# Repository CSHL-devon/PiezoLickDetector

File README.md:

# Piezo Lick Detector

An amplifier for detecting rodent licks using piezo-based sensor systems

## General Use

Each board has three channels that can receive separate input from three different piezo sensors. Each channel has independently controllable gain and dual outputs: raw analog voltage and 5V TTL.

### Piezo Concerns

- We use 12mm piezo disks that are extremely common and cheap. 

- "Positive" input on the amp is considered the crystal side of the piezo (the white center of the disk/strip) and "negative" the surrounding copper. If you wire it backwards, you will still get a signal (piezo output is AC), but it may not be the side of the signal you want. The amp cuts anything below zero as it enters the circuit, so depending on the orientation of the piezo in the sensor, or with respect to the animal, the "positive" voltage swing may be bigger, or smaller than the "negative" swing when the animal licks. Best practice is just to test output response once the system is in place and wire it the way you get the biggest signal.

- If you're solding the wires to the piezo yourself, take care not to overheat the piezo. Even if it doesn't visibly delaminate the piezo, you could do enough unseen damage to end up with a poor sensor. If you're not confident in your soldering skills, piezos are available pre-wired.

- This is a voltage-mode piezo amp. The length of the wire between the piezo and the amp should be kept to a minimum, else the capacitance of the cable will start to interfere with the sensor.

### Gain

The gain of the amplifier is adjusted using the round trimmer marked "Gain" for the appropriate channel. This trimmer is multi-turn to add some precision to the adjustments, however it has no stops to indicate the start, or end of the range. On first use, it's a good idea to simply turn it counter-clockwise several (~10) full turns to be sure you're at the bottom and then slowly work your way up until you reach the desired signal.  

Choosing the correct gain can be tricky with piezo-based systems and the quality of the detection you get will depend on the type of piezo/lick-spout you deploy, the placement of your sensor with respect to the animal and how well the sensor is physically isolated from other sources of shock/vibration. This is not trivial and takes some practice to get your setup and positioning perfect. 

### Threshold

The 5V TTL output is based on thresholding the raw voltage signal. That threshold is controlled using the square single-turn trimmer labeled "Threshold" for the appropriate channel. The available threshold does not cover the entire 0-5V range of the device. By default, it covers 2.5V-3.75V. This range was found (for our purposes) to encompass the best gain settings for noise when the setup is well optimized. You can, of course alter the range by changing the values of R2, R9 and R10 (as an example for channel 1) if you find it doesn't suit your use-case, but the default is a good starting point. You could also just bring the raw signal in through a DAQ and threshold in software if that suits your setup design.

## Building

This project came before I started converting all my projects to through-hole, so most of the parts are surface-mount. It's not too bad and If you practice a bit with a rework station you can get through it. If you have access to a surface-mount oven it's easy. Otherwise, there are many services that will populate the board with the parts for you. 

I may eventually get around to updating this to through-hole construction, but you can also just build it on a breadboard, or an Adafruit perma-proto board by following the schematic, without the custom PCB. This is probably the easiest way to get up and running for the least money and all of the parts I've used have through-hole equivalents.

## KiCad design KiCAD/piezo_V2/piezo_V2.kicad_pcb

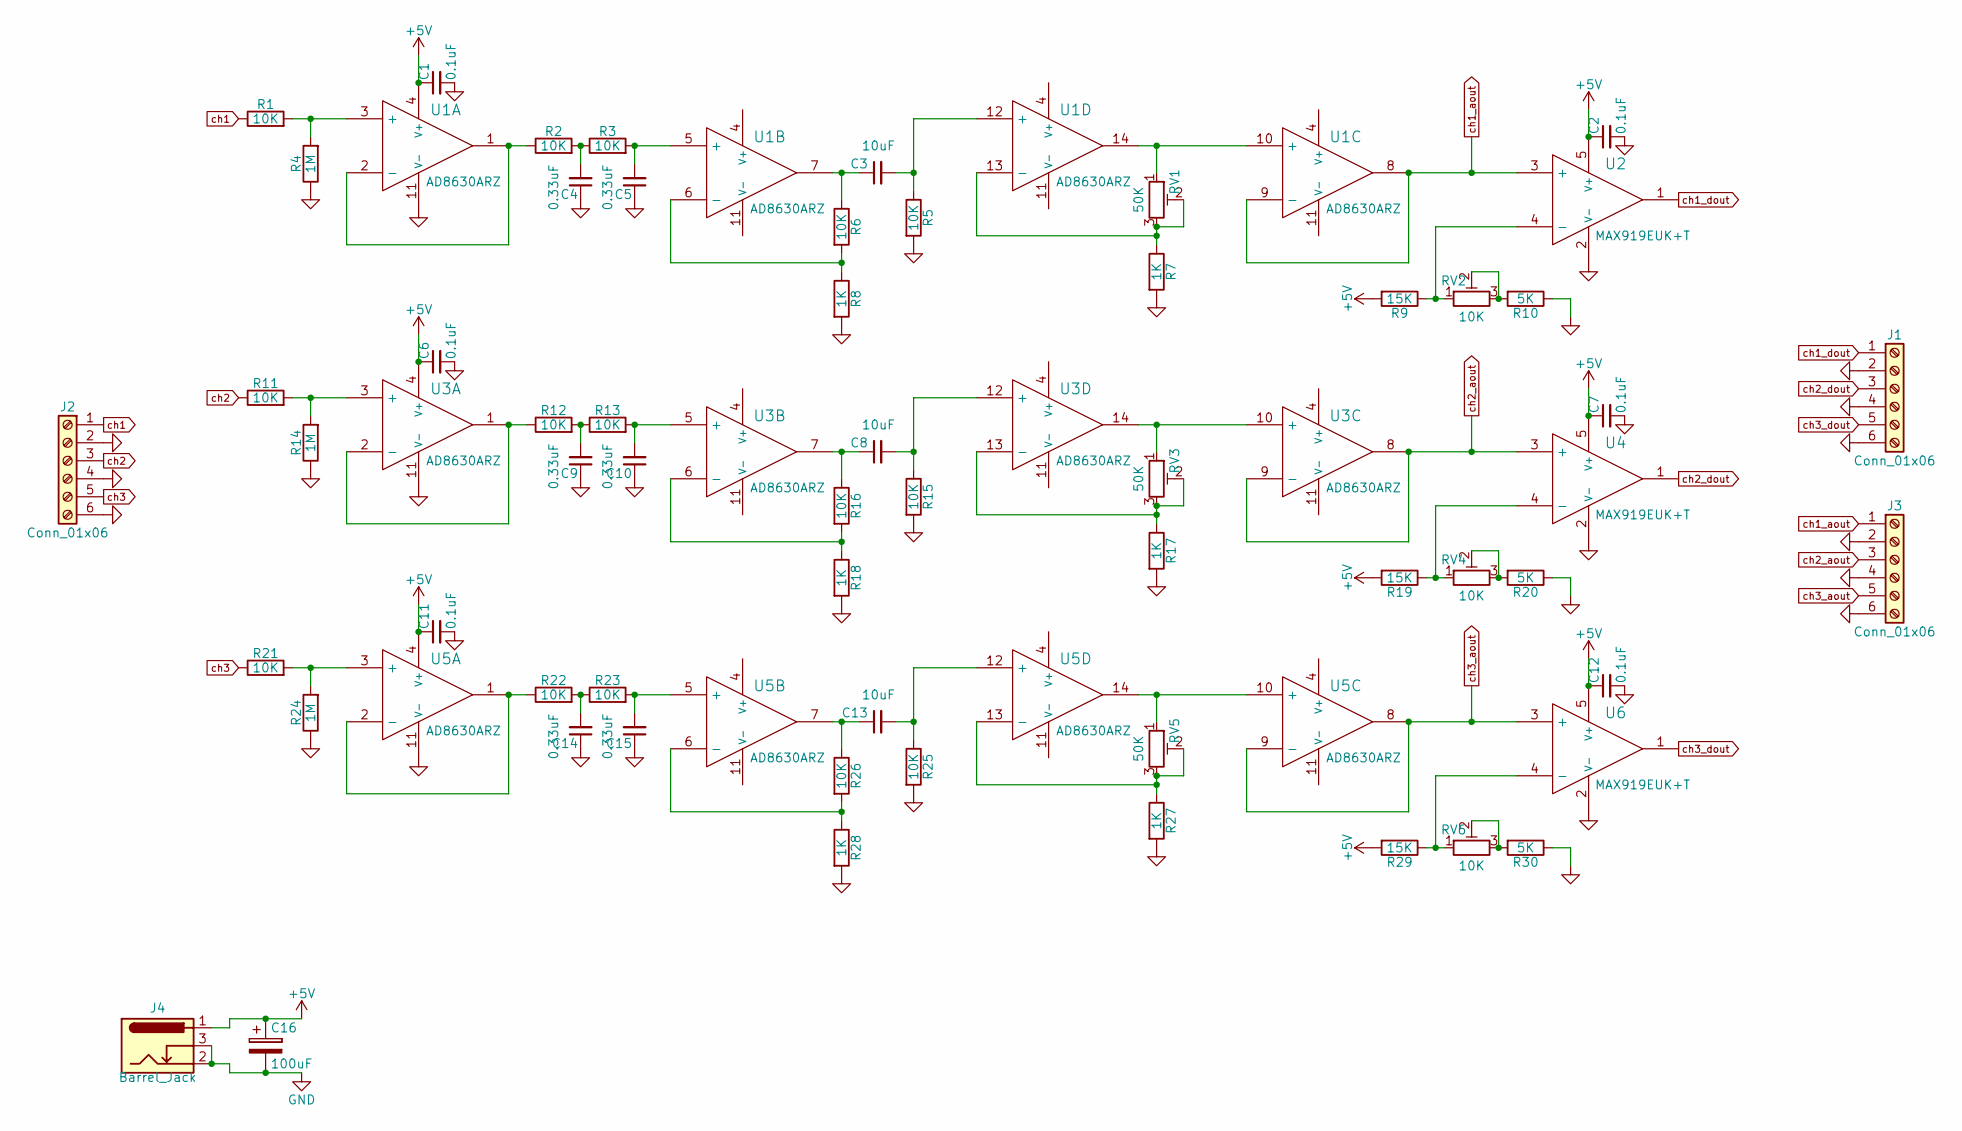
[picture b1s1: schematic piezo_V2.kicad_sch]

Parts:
C1, C2, C6, C7, C11, C12: 0.1uF; C_1206_HandSoldering
C3, C8, C13: 10uF; C_1206_HandSoldering
C4, C5, C9, C10, C14, C15: 0.33uF; C_1206_HandSoldering
C16: 100uF; CP_Radial_D8.0mm_P3.50mm
J1, J2, J3: Conn_01x06; EM280206_6P_Terminal
J4: Barrel_Jack; PJ-079AH-DCJACK
R1, R2, R3, R5, R6, R11, R12, R13, R15, R16, R21, R22, R23, R25, R26: 10K; R_1206_HandSoldering
R4, R14, R24: 1M; R_1206_HandSoldering
R7, R8, R17, R18, R27, R28: 1K; R_1206_HandSoldering
R9, R19, R29: 15K; R_1206_HandSoldering
R10, R20, R30: 5K; R_1206_HandSoldering
RV1, RV3, RV5: 50K; 50K_Trimmer_Bourns_3339P
RV2, RV4, RV6: 10K; 10K_Trimmer_Bourns_3362P
U1, U3, U5: AD8630ARZ
U2, U4, U6: MAX919EUK+T; TMAX9140EUK+T

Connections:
+5V: C1.1, C2.1, C6.1, C7.1, C11.1, C12.1, C16.1, J4.1, R9.2, R19.2, R29.2, U1.4 (V+), U2.5 (V+), U3.4 (V+), U4.5 (V+), U5.4 (V+), U6.5 (V+)
GND: C1.2, C2.2, C4.1, C5.1, C6.2, C7.2, C9.1, C10.1, C11.2, C12.2, C14.1, C15.1, C16.2, J1.2, J1.4, J1.6, J2.2, J2.4, J2.6, J3.2, J3.4, J3.6, J4.2, J4.3, R4.1, R5.2, R7.2, R8.2, R10.1, R14.1, R15.2, R17.2, R18.2, R20.1, R24.1, R25.2, R27.2, R28.2, R30.1, U1.11 (V-), U2.2 (V-), U3.11 (V-), U4.2 (V-), U5.11 (V-), U6.2 (V-)
unnamed: C3.1, R6.1, U1.7
unnamed: C3.2, R5.1, U1.12 (+)
unnamed: C4.2, R2.2, R3.1
unnamed: C5.2, R3.2, U1.5 (+)
unnamed: C8.1, R16.1, U3.7
unnamed: C8.2, R15.1, U3.12 (+)
unnamed: C9.2, R12.2, R13.1
unnamed: C10.2, R13.2, U3.5 (+)
unnamed: C13.1, R26.1, U5.7
unnamed: C13.2, R25.1, U5.12 (+)
unnamed: C14.2, R22.2, R23.1
unnamed: C15.2, R23.2, U5.5 (+)
unnamed: R1.2, R4.2, U1.3 (+)
unnamed: R2.1, U1.1, U1.2 (-)
unnamed: R6.2, R8.1, U1.6 (-)
unnamed: R7.1, RV1.2, RV1.3, U1.13 (-)
unnamed: R9.1, RV2.1, U2.4 (-)
unnamed: R10.2, RV2.2, RV2.3
unnamed: R11.2, R14.2, U3.3 (+)
unnamed: R12.1, U3.1, U3.2 (-)
unnamed: R16.2, R18.1, U3.6 (-)
unnamed: R17.1, RV3.2, RV3.3, U3.13 (-)
unnamed: R19.1, RV4.1, U4.4 (-)
unnamed: R20.2, RV4.2, RV4.3
unnamed: R21.2, R24.2, U5.3 (+)
unnamed: R22.1, U5.1, U5.2 (-)
unnamed: R26.2, R28.1, U5.6 (-)
unnamed: R27.1, RV5.2, RV5.3, U5.13 (-)
unnamed: R29.1, RV6.1, U6.4 (-)
unnamed: R30.2, RV6.2, RV6.3
unnamed: RV1.1, U1.10 (+), U1.14
unnamed: RV3.1, U3.10 (+), U3.14
unnamed: RV5.1, U5.10 (+), U5.14
ch1: J2.1, R1.1
ch1_aout: J3.1, U1.8, U1.9 (-), U2.3 (+)
ch1_dout: J1.1, U2.1
ch2: J2.3, R11.1
ch2_aout: J3.3, U3.8, U3.9 (-), U4.3 (+)
ch2_dout: J1.3, U4.1
ch3: J2.5, R21.1
ch3_aout: J3.5, U5.8, U5.9 (-), U6.3 (+)
ch3_dout: J1.5, U6.1

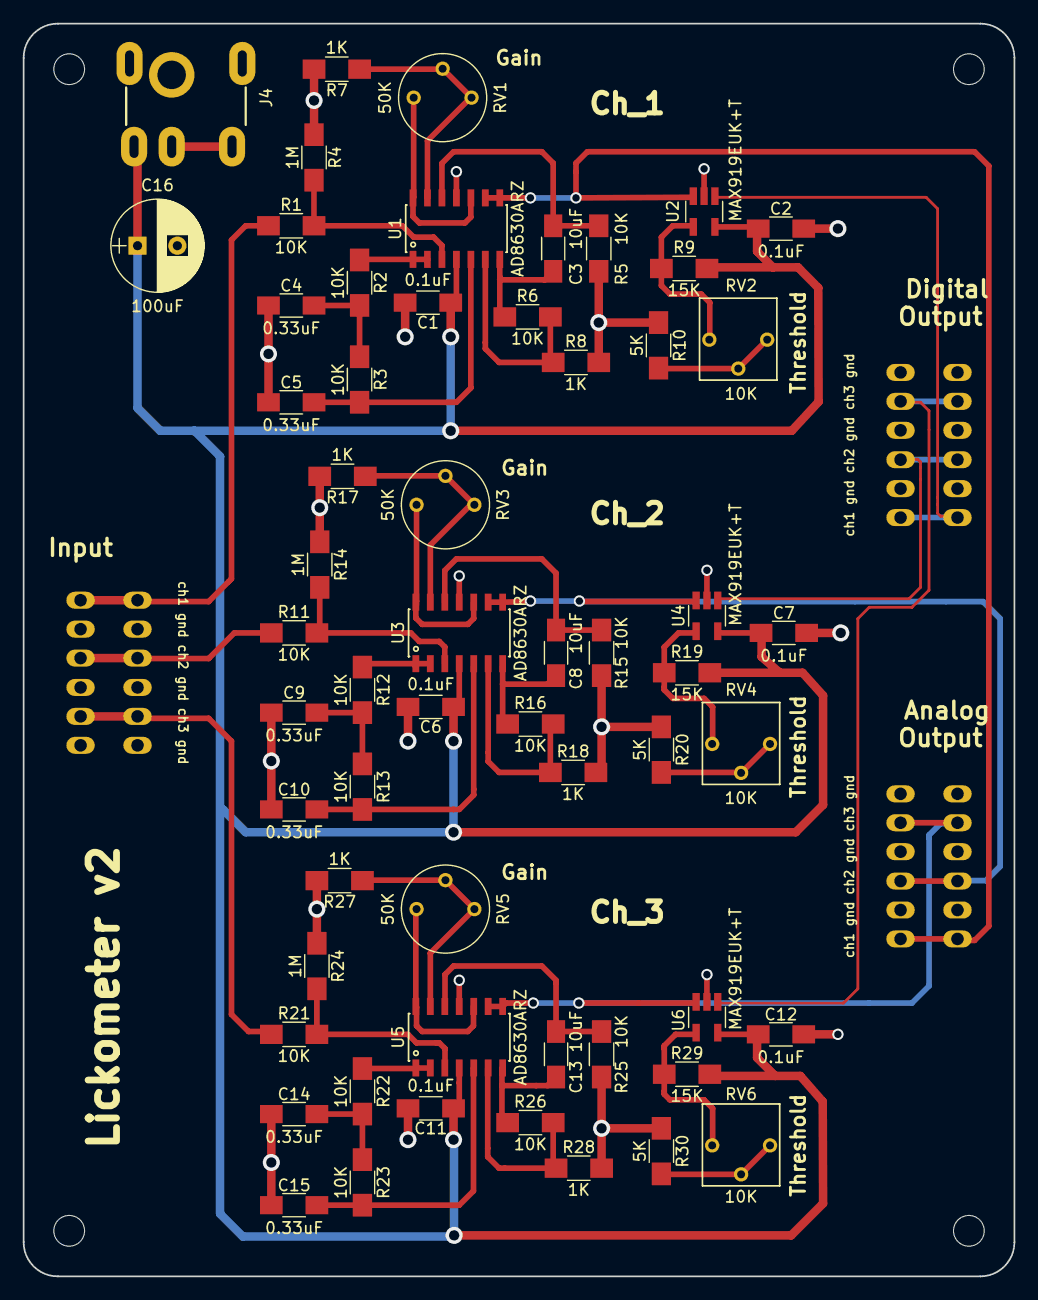
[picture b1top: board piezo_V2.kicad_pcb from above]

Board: 2 copper layers, 87.0 x 110.0 mm, 62 parts (0 on the bottom side), 44 nets.

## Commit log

2024-01-17 Add README, Update Symbols on Schematic
2024-04-03 Final CSHL
